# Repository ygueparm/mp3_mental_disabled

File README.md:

# mp3 player for mental disabled
mp3_mental_disabled is a simplified MP3 speaker designed for people with intellectual disabilities. It focuses on ease of use, minimal controls, and clear audio playback. The project aims to provide an accessible, reliable, and stress-free music experience using simple hardware and software.

##  MP3 Player for People with Mental Disabilities

One of my daughters is 80% mentally disabled. To give you an idea, at 20 years old she has the IQ of a 3-4 year old child.

She can learn certain things, but it takes quite a bit of time. We leave her an MP3 speaker because she loves listening to music.

The problem: These speakers have 3 buttons, and depending on how long you press them, the function changes. When she wants to change the song, she presses pretty much everything and switches the speaker to radio or Bluetooth mode, and I have to put it back in the right mode quite regularly. I don't have time for just that!

I'm using an Attiny85 as an interface between the MP3 PCB and the human to simulate the correct button presses and limit them to next+ and volume down.

I was inspired by jbd's journal at https://linuxfr.org/users/jbd/journaux/hacking-d-une-machine-a-pain
The point that was giving me trouble was using optocouplers. I found something better! No optocouplers needed!

Since the inputs are active low, I use the Tiny's LOW output, and for "no press" I set the pin as an input (so in high impedance state).

To pull to ground:
```
cpp

void setPinLow(uint8_t pin) {
  digitalWrite(pin, LOW);
  pinMode(pin, OUTPUT);
}

**Important:** set to LOW BEFORE switching to output mode

And to float (high impedance):
cpp

void setPinHighZ(uint8_t pin) {
  pinMode(pin, INPUT);
  digitalWrite(pin, LOW); // (just in case)
}
```

So no optocoupler and I'm using 4 pins out of 6 on the Tiny. At startup, I increase the volume, then I limit button presses.
The next track can only be selected after 5 seconds, so she actually listens a bit before changing :)

It's possible to completely mute the sound, but a simple power cycle restores the volume level.
To increase the volume more and more, just do several power cycles in a row.

In short: simple, effective, and it gives the person autonomy. If I tell her to stop the music, she can do it, change tracks, lower the volume too.

And she can stop it herself to go to sleep. IN SHORT: it's brilliant!

## list of equipment

### I particularly recommend the French manufacturer of polycarbonate boxes, which are resistant and unbreakable schneider electrique :
The cover is closed with four captive flat screws located outside the sealed area of the enclosure to maintain the IP rating. It is TÜV and UL certified and is fire resistant up to 960°C in accordance with IEC 62208. It offers high protection against dust and water with an IP66 rating (NEMA 4.4X). It is impact resistant (IK08 rating, IEC 62262). It also has Class II electrical insulation, which prevents electric shocks and offers fully insulated solutions. It can be stored at temperatures between -15 and 60°C and used between -25 and 80°C without affecting its performance. you can use it even in siberia ! :)

 *  https://www.se.com/fr/fr/product/NSYTBP16128/panelset-bo%C3%AEte-industrielle-164x121x87mm-pc/
 *  PanelSeT - boîte industrielle - 164x121x87mm - PCNSYTBP16128

 *  1Pcs Metal Round Socket Module
 *  https://fr.aliexpress.com/item/1005005363341111.html

 *  AIYIMA 2 pièces 2 "pouces 4 Ohm 3W gamme
 *  https://fr.aliexpress.com/item/32593991938.html

 *  https://fr.aliexpress.com/item/1005007445592831.html
 * 
 *  Ttiny85 Digispark Kickstarter Micro USB
 *  https://fr.aliexpress.com/item/1005009004637470.html

 *  Audio MP3 TF 2W 5V
 *  https://fr.aliexpress.com/item/1005009187267335.html

Why choose the Tiny85? I always feel a bit bad using only 4 pins out of 40 on a microcontroller. Low power consumption, 1MHz speed, variable supply voltage. Very flexible to use and very cheap. A bit difficult to program because you need an Arduino in ISP mode as an interface between the Tiny and Arduino IDE.

# Small production

Now the project is very well and my daughter is very happy but it take 2 to 3 hours to make one, for small production i made a mother board
for reduce the time for it. time to time and buold one for this friends, and some young children like it very much (2 to 5 years old) !

 this pcb can spped up your box, only 10 to 15 min to finish one instead 2 a 3h, this pcb let you choose wich chip you prefer, small board with Attiny85, chip attiny85, STM8, CH32V003A4M6, the last one cost only 0.20€ and you can use arduino-ide for programming it
 
 YOU NEED ONLY ONE OF THIS CHIP AT ONCE : attiny85, STM8, CH32V003A4M6 simply choose wich you prefer

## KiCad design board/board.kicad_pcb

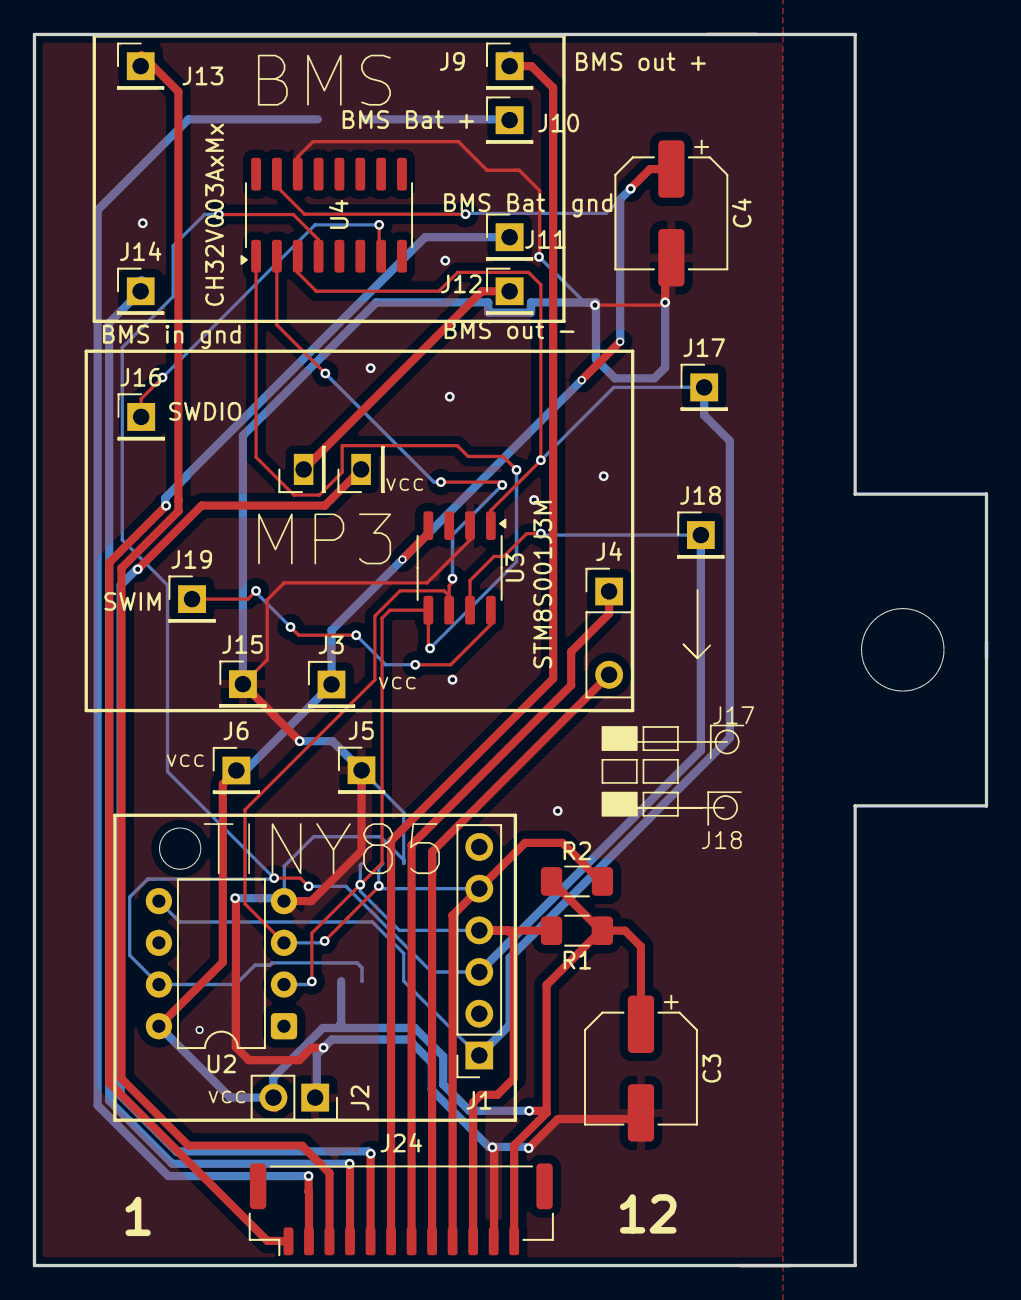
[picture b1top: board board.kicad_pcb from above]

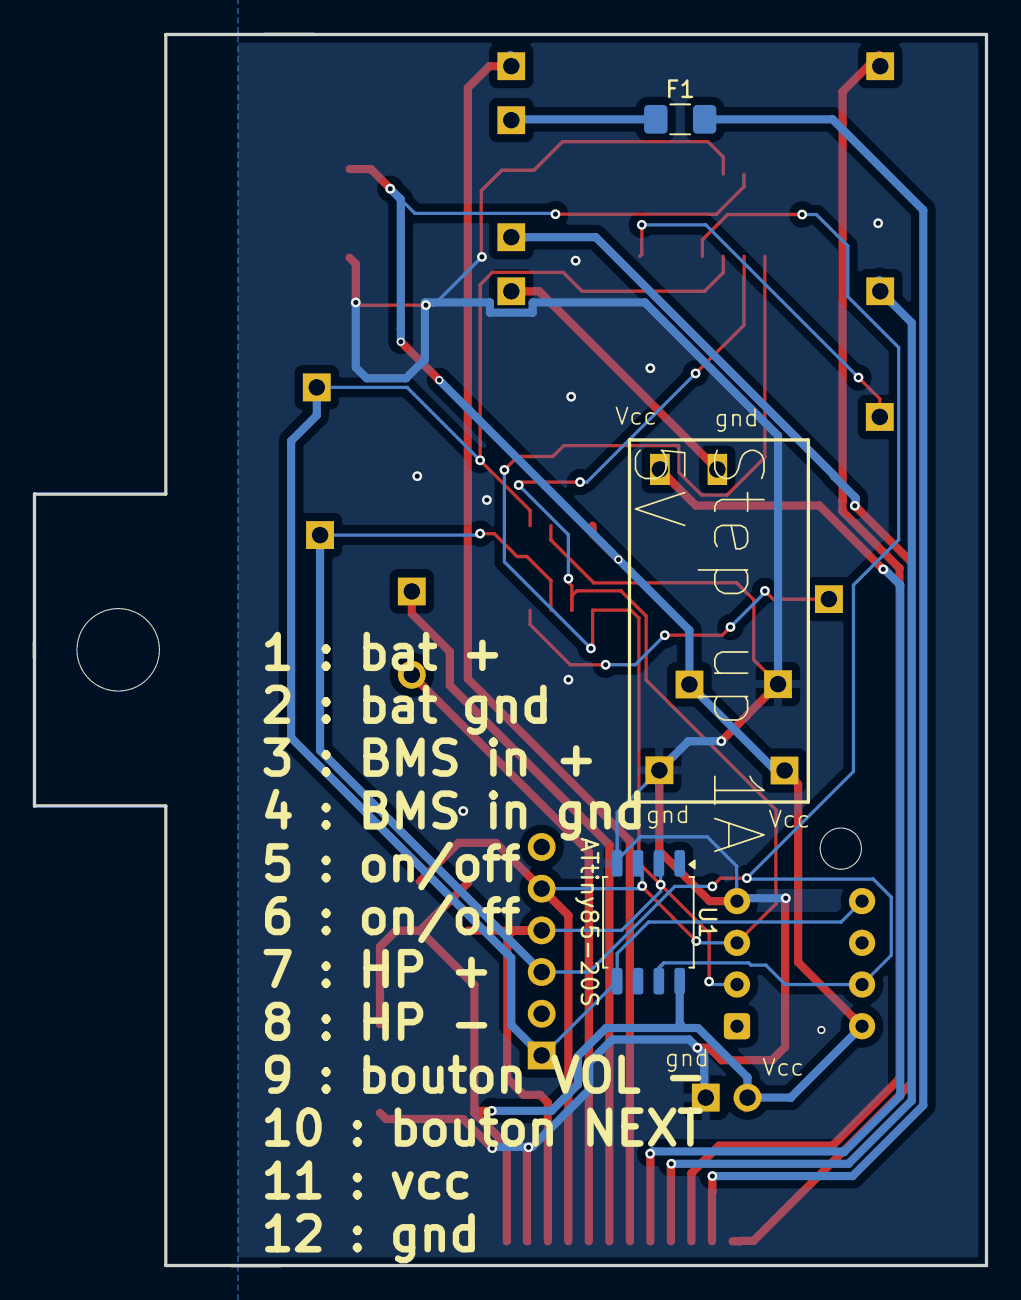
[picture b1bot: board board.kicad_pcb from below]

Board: 2 copper layers, 58.0 x 75.0 mm, 29 parts (2 on the bottom side), 18 nets.

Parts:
C3, C4: C_C22388053; CP_Elec_6.3x7.7
F1: Fuse C2760306; Fuse_1206_3216Metric_Pad1.42x1.75mm_HandSolder
J1: port attiny; PinSocket_1x06_P2.54mm_Vertical
J2: Conn_01x02_Pin; PinSocket_1x02_P2.54mm_Vertical
J3: alim mp3 +; PinHeader_1x01_P2.54mm_Vertical
J4: hp mp3; PinHeader_1x03_P2.54mm_Vertical-mp3
J5: step out - gnd; PinHeader_1x01_P2.54mm_Vertical
J6: step up out+; PinHeader_1x01_P2.54mm_Vertical
J7: step up in +; PinHeader_1x01_P2.54mm_Vertical
J8: step up in -; PinHeader_1x01_P2.54mm_Vertical
J9: BMS out +; PinHeader_1x01_P2.54mm_Vertical
J10: BMS Bat +; PinHeader_1x01_P2.54mm_Vertical
J11: BMS Bat gnd; PinHeader_1x01_P2.54mm_Vertical
J12: BMS out -; PinHeader_1x01_P2.54mm_Vertical
J13: BMS in +5v; PinHeader_1x01_P2.54mm_Vertical
J14: BMS in gnd; PinHeader_1x01_P2.54mm_Vertical
J15: alim mp3 -; PinHeader_1x01_P2.54mm_Vertical
J16: SWDIO; PinHeader_1x01_P2.54mm_Vertical
J17: next; PinHeader_1x01_P2.54mm_Vertical
J18: vol -; PinHeader_1x01_P2.54mm_Vertical
J19: SWIM; PinHeader_1x01_P2.54mm_Vertical
J24: port 3-C265421; JST_GH_BM12B-GHS-TBT_1x12-1MP_P1.25mm_Vertical
R1, R2: 4.7kΩ _C17936; R_1206_3216Metric_Pad1.30x1.75mm_HandSolder
U1: ATtiny85-20S; SOIC-8_5.3x5.3mm_P1.27mm
U2: ATtiny85V-10P; DIP-8_W7.62mm
U3: STM8S001J3M; SO-8_3.9x4.9mm_P1.27mm
U4: CH32V003AxMx; SOP-16_3.9x9.9mm_P1.27mm

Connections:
BMS in +: J13.1, J24.3
BMS in gnd: J14.1, J24.4
BMS out -: J8.1, J12.1
GND: C3.2, C4.2, J2.1, J5.1, J15.1, J24.11, U1.4 (GND), U2.4 (GND), U3.2 (VSS), U4.14 (VSS)
HP +: J4.1, J24.7
HP -: J4.2, J24.8
unnamed: F1.1, J10.1
unnamed: J16.1, U4.7 (PD1)
unnamed: J19.1, U3.8 (PD5)
Next + mp3: J1.1, J17.1, U1.5 (AREF/PB0), U2.5 (AREF/PB0), U3.1 (PD6), U4.3 (PC3)
VCC: C3.1, C4.1, J2.2, J3.1, J6.1, J24.12, R1.1, R2.1, U1.8 (VCC), U2.8 (VCC), U3.4 (VDD), U4.15 (VDD)
bat +: J11.1, J24.1
bat gnd: F1.2, J24.2
bouton NEXT: J1.4, J24.10, R1.2, U1.2 (XTAL1/PB3), U2.2 (XTAL1/PB3), U3.5 (PB5), U4.1 (PC1)
bouton VOL -: J1.5, J24.9, R2.2, U1.3 (XTAL2/PB4), U2.3 (XTAL2/PB4), U3.6 (PB4), U4.2 (PC2)
on/off in: J9.1, J24.6
on/off out: J7.1, J24.5
vol - mp3: J1.3, J18.1, U1.7 (PB2), U2.7 (PB2), U3.7 (PC5), U4.4 (PC4)

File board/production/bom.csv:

Designator,Footprint,Quantity,Value,LCSC Part #
"C3, C4",CP_Elec_6.3x7.7,2,C_C22388053,
F1,1206,1,Fuse C2760306,
J1,PinSocket_1x06_P2.54mm_Vertical,1,port attiny,
J10,PinHeader_1x01_P2.54mm_Vertical,1,BMS Bat +,
J11,PinHeader_1x01_P2.54mm_Vertical,1,BMS Bat  gnd,
J12,PinHeader_1x01_P2.54mm_Vertical,1,BMS out -,
J13,PinHeader_1x01_P2.54mm_Vertical,1,BMS in +5v,
J14,PinHeader_1x01_P2.54mm_Vertical,1,BMS in gnd,
J15,PinHeader_1x01_P2.54mm_Vertical,1,alim mp3 -,
J16,PinHeader_1x01_P2.54mm_Vertical,1,SWDIO,
J17,PinHeader_1x01_P2.54mm_Vertical,1,next,
J18,PinHeader_1x01_P2.54mm_Vertical,1,vol -,
J19,PinHeader_1x01_P2.54mm_Vertical,1,SWIM,
J2,PinSocket_1x02_P2.54mm_Vertical,1,Conn_01x02_Pin,
J24,JST_GH_BM12B-GHS-TBT_1x12-1MP_P1.25mm_Vertical,1,port 3-C265421,
J3,PinHeader_1x01_P2.54mm_Vertical,1,alim mp3 +,
J4,PinHeader_1x03_P2.54mm_Vertical-mp3,1,hp mp3,
J5,PinHeader_1x01_P2.54mm_Vertical,1,step out -  gnd,
J6,PinHeader_1x01_P2.54mm_Vertical,1,step up out+,
J7,PinHeader_1x01_P2.54mm_Vertical,1,step up in +,
J8,PinHeader_1x01_P2.54mm_Vertical,1,step up in -,
J9,PinHeader_1x01_P2.54mm_Vertical,1,BMS out +,
"R1, R2",1206,2,4.7kΩ _C17936,
U1,SOIC-8_5.3x5.3mm_P1.27mm,1,ATtiny85-20S,
U2,DIP-8_W7.62mm,1,ATtiny85V-10P,
U3,SO-8_3.9x4.9mm_P1.27mm,1,STM8S001J3M,
U4,SOP-16_3.9x9.9mm_P1.27mm,1,CH32V003AxMx,

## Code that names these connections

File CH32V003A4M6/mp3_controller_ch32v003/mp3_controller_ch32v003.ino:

/*
 * Contrôleur MP3 Minimaliste — CH32V003A4M6
 * Transposé depuis ATtiny85 v3.4
 * Architecture: RISC-V 32 bits, 48 MHz (réduit à ~1 MHz via prescaler)
 *
 * === MAPPING DES BROCHES ===
 *
 * | Fonction        | ATtiny85 | CH32V003A4M6 | Broche physique |
 * |-----------------|----------|--------------|-----------------|
 * | Bouton Next     | PB3      | C1 (PC1)     | pin 1           |
 * | Bouton Vol-     | PB4      | C2 (PC2)     | pin 2           |
 * | Sortie KEY      | PB2      | C3 (PC3)     | pin 3           |
 * | Sortie KEY_VOL- | PB0      | C4 (PC4)     | pin 4           |
 *
 * === NOTES D'ADAPTATION ===
 * - Le CH32V003 n'a pas de mode 1 MHz natif. On garde 48 MHz mais
 *   les délais restent corrects grâce à delay() qui est calibré.
 * - Open-drain : le CH32V003 supporte le mode OUTPUT_OPEN_DRAIN
 *   via pinMode(pin, OUTPUT_OPEN_DRAIN). Si ton core ne le supporte
 *   pas, la méthode setPinLow/setPinHighZ reste compatible.
 * - Les numéros de broches ci-dessous suivent la numérotation
 *   Arduino du core CH32 WCH. Adapte si tu utilises ch32v003fun.
 *
 * === ALIMENTATION ===
 * - 3.3V (idem ATtiny85 en 3.3V)
 * - Consommation plus élevée qu'ATtiny85 (~5 mA actif vs ~0.3 mA)
 */

// --- Broches (numérotation Arduino, core CH32 WCH) ---
// PD4 = Arduino pin 4 sur CH32V003 (à vérifier selon ton core)
const uint8_t BTN_NEXT    = C1;   // Bouton Next Track (entrée, pull-up)
const uint8_t BTN_VOL_D   = C2;   // Bouton Volume -   (entrée, pull-up)
const uint8_t KEY_TRACK   = C3;   // Sortie vers KEY du MP3 (Next / Vol+)
const uint8_t KEY_VOLDOWN = C4;   // Sortie vers KEY_VOLDOWN du MP3

// --- Durées de pulse (inchangées) ---
const uint16_t PULSE_NEXT     = 250;   // ms — next track sur KEY_TRACK
const uint16_t PULSE_VOL_UP   = 2500;  // ms — volume + sur KEY_TRACK (setup)
const uint16_t PULSE_VOL_DOWN = 1500;  // ms — volume - sur KEY_VOLDOWN

// --- Timing ---
const uint16_t MP3_BOOT_DELAY  = 1000; // ms — attente démarrage module MP3
const uint16_t DEBOUNCE_DELAY  = 50;   // ms — anti-rebond
const uint16_t COOLDOWN_NEXT   = 4000; // ms — délai min entre deux Next
const uint16_t COOLDOWN_VOL_D  = 2000; // ms — délai min entre deux Vol-

// --- État bouton Next ---
uint8_t  lastBtnStateNext    = HIGH;
uint32_t lastDebounceTimeNext = 0;
uint8_t  btnStateNext         = HIGH;
uint32_t lastActionTimeNext   = 0;

// --- État bouton Vol- ---
uint8_t  lastBtnStateVolD    = HIGH;
uint32_t lastDebounceTimeVolD = 0;
uint8_t  btnStateVolD         = HIGH;
uint32_t lastActionTimeVolD   = 0;

// ---------------------------------------------------------------------------
// Pilotage open-drain : LOW actif, haute impédance au repos
// Compatible avec les deux méthodes (OUTPUT_OPEN_DRAIN ou INPUT flottant)
// ---------------------------------------------------------------------------

void setPinLow(uint8_t pin) {
    digitalWrite(pin, LOW);
    pinMode(pin, OUTPUT);
}

void setPinHighZ(uint8_t pin) {
    pinMode(pin, INPUT);      // haute impédance — la résistance de tirage
    digitalWrite(pin, LOW);   // du module MP3 remonte la ligne
}

void setPinInput(uint8_t pin) {
    pinMode(pin, INPUT_PULLUP);
}

// Génère une impulsion LOW de durée 'duration' ms
void sendPulse(uint8_t pin, uint16_t duration) {
    setPinLow(pin);
    delay(duration);
    setPinHighZ(pin);
}

// ---------------------------------------------------------------------------
// Anti-rebond + détection front descendant (HIGH → LOW)
// Identique à l'ATtiny85 — millis() fonctionne de la même façon
// ---------------------------------------------------------------------------

bool buttonFell(uint8_t pin,
                uint8_t  &lastState,
                uint32_t &lastDebounceTime,
                uint8_t  &currentState)
{
    uint8_t  reading = digitalRead(pin);
    uint32_t now     = millis();

    if (reading != lastState) {
        lastDebounceTime = now;
    }

    if ((now - lastDebounceTime) > DEBOUNCE_DELAY) {
        if (reading != currentState) {
            currentState = reading;
            if (currentState == LOW) {
                lastState = reading;
                return true;
            }
        }
    }

    lastState = reading;
    return false;
}

// Vérifie que le cooldown est écoulé depuis la dernière action
bool canTriggerAction(uint32_t &lastActionTime, uint16_t cooldownDelay) {
    uint32_t now = millis();

    // Gestion débordement millis() (~49 jours)
    if (now < lastActionTime) {
        lastActionTime = now;
        return true;
    }

    return ((now - lastActionTime) >= cooldownDelay);
}

// ---------------------------------------------------------------------------
// Setup
// ---------------------------------------------------------------------------

void setup() {
    // Entrées avec pull-up interne
    setPinInput(BTN_NEXT);
    setPinInput(BTN_VOL_D);

    // Sorties en haute impédance au repos
    setPinHighZ(KEY_VOLDOWN);
    setPinHighZ(KEY_TRACK);

    // Lecture initiale des boutons
    lastBtnStateNext = digitalRead(BTN_NEXT);
    lastBtnStateVolD = digitalRead(BTN_VOL_D);
    btnStateNext     = lastBtnStateNext;
    btnStateVolD     = lastBtnStateVolD;

    // Init des timers
    uint32_t now       = millis();
    lastDebounceTimeNext = now;
    lastDebounceTimeVolD = now;
    lastActionTimeNext   = 0;
    lastActionTimeVolD   = 0;

    // Attendre le démarrage du module MP3
    delay(MP3_BOOT_DELAY);

    // Augmentation volume au démarrage (décommenter si nécessaire)
    // sendPulse(KEY_TRACK, PULSE_VOL_UP);
    // delay(500);
}

// ---------------------------------------------------------------------------
// Boucle principale (identique à l'ATtiny85)
// ---------------------------------------------------------------------------

void loop() {
    // Bouton Next Track (cooldown 4 s)
    if (buttonFell(BTN_NEXT, lastBtnStateNext, lastDebounceTimeNext, btnStateNext)) {
        if (canTriggerAction(lastActionTimeNext, COOLDOWN_NEXT)) {
            sendPulse(KEY_TRACK, PULSE_NEXT);
            lastActionTimeNext = millis();
        }
    }

    // Bouton Volume - (cooldown 2 s)
    if (buttonFell(BTN_VOL_D, lastBtnStateVolD, lastDebounceTimeVolD, btnStateVolD)) {
        if (canTriggerAction(lastActionTimeVolD, COOLDOWN_VOL_D)) {
            sendPulse(KEY_VOLDOWN, PULSE_VOL_DOWN);
            lastActionTimeVolD = millis();
        }
    }

    delay(5);
}

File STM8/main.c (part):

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 * Flashé avec  : stm8flash -c stlinkv2 -p stm8s001j3 -w main.ihx
 *
 * Mapping des broches (boîtier SO8) :
 *  PD5 (pin 1) → BTN_NEXT    (entrée, pull-up interne)
 *  PA1 (pin 2) → non utilisé  (sortie push-pull, forcée à 0)
 *  PA2 (pin 3) → non utilisé  (sortie push-pull, forcée à 0)
 *  PA3 (pin 4) → non utilisé  (sortie push-pull, forcée à 0)
 *  PC3 (pin 5) → KEY_VOLDOWN (sortie open-drain)
 *  PC4 (pin 6) → KEY_TRACK   (sortie open-drain)
 *  PC5 (pin 7) → BTN_VOL_D   (entrée, pull-up interne) ← SWIM libre sur PD1
 *  PD6 (pin 8) → non utilisé  (sortie push-pull, forcée à 0)
 *
 * Horloge : HSI 16 MHz / 32 = 500 kHz (CLK_CKDIVR = 0x1B)
 *
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/* Broches                                                             */
/* ------------------------------------------------------------------ */

#define BTN_NEXT_BIT     5   /* PD5 — bouton Next Track  */
#define BTN_VOLD_BIT     5   /* PC5 — bouton Volume -    */
#define KEY_VOLDOWN_BIT  3   /* PC3 — sortie vol-        */
#define KEY_TRACK_BIT    4   /* PC4 — sortie next/vol+   */

#define BTN_NEXT_READ()   ((PD_IDR >> BTN_NEXT_BIT) & 1)
#define BTN_VOLD_READ()   ((PC_IDR >> BTN_VOLD_BIT) & 1)
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     * Broches non utilisées → sortie push-pull forcée à 0
     * (évite les commutations parasites et la consommation associée)
     * PA1, PA2, PA3 : DDR=1 (sortie), CR1=1 (push-pull), ODR=0
     * PD6           : DDR=1 (sortie), CR1=1 (push-pull), ODR=0
     * ---------------------------------------------------------------- */
    PA_ODR &= ~((1 << 1) | (1 << 2) | (1 << 3));
    PA_DDR |=   (1 << 1) | (1 << 2) | (1 << 3);
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    PD_CR2 &= ~(1 << 6);

    /* ----------------------------------------------------------------
     * PD5 : BTN_NEXT — entrée avec pull-up interne
     * DDR=0 (entrée), CR1=1 (pull-up), CR2=0 (pas d'IRQ)
     * ---------------------------------------------------------------- */
    PD_DDR &= ~(1 << BTN_NEXT_BIT);
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    PD_CR2 &= ~(1 << BTN_NEXT_BIT);

    /* ----------------------------------------------------------------
     * PC5 : BTN_VOLD — entrée avec pull-up interne
     * PC3, PC4 : open-drain au repos (haute impédance, DDR=0, CR1=0)
     * ---------------------------------------------------------------- */
    PC_DDR &= ~((1 << BTN_VOLD_BIT) | (1 << KEY_VOLDOWN_BIT) | (1 << KEY_TRACK_BIT));
    PC_CR1 |=  (1 << BTN_VOLD_BIT);
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    /* delay_ms(500); */

    for (;;) {
        /* Bouton Next Track (PD5) */
        if (button_fell(BTN_NEXT_READ(),
                        &lastStateNext, &debounceNext, &btnStateNext)) {
            if (can_trigger(&lastActionNext, COOLDOWN_NEXT)) {
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            }
        }

        /* Bouton Volume - (PC5) */
        if (button_fell(BTN_VOLD_READ(),
                        &lastStateVolD, &debounceVolD, &btnStateVolD)) {
            if (can_trigger(&lastActionVolD, COOLDOWN_VOLD)) {
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
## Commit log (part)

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2026-01-16 readme add
2026-01-16 add .ino
2026-01-16 add jpg
2026-01-17 Add files via upload
    synoptic
2026-01-17 Add files via upload
    plan
2026-01-17 Add files via upload
    photo project
2026-04-30 pcb carte mere
2026-05-01 ajout +5v + resistance de tirage
2026-05-03 pcb carte mere mise a jour
2026-05-03 copie ecran pcb + modif positionnement pad
2026-05-03 copie ecran new pcb
2026-05-03 correct readme
2026-05-21 mise a jour pcb
2026-05-22 correction pcb , ajout copie d'ecran, et modification readme
2026-05-22 correction sens pin vue 3D
2026-05-22 ajout serigraphie pour faciliter le montage
2026-05-22 mise a jour marquage pcb et ajout programation tiny dans le source
2026-05-25 ajout connecteur programmation tiny85
2026-05-25 modif readme, ajout copie ecran sch
2026-06-07 mise a jour pcb routage pour reduire la taille
2026-06-08 ajout etiquette global + plan de masse
2026-06-11 ajout empreinte STM8 + CH32V0003
2026-06-12 correction inversion polarité sur l'alimentation
2026-06-20 mise a jour marquage pcb et ajout programation tiny dans le source, ajout autre famille ucontrolleur STM8 et wch
2026-06-20 mise a jour
